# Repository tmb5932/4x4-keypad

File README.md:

# My 4x4 Keypad
This Repo contains the KiCad files of a 4 by 4 Keypad that I personally designed and created (with some help from various KiCad tutorials).

The purpose of this keypad was to bring my Chip8 Emulator to life without taking the easy way out and buying a premade one.

## Author
Travis Brown (tmb5932)

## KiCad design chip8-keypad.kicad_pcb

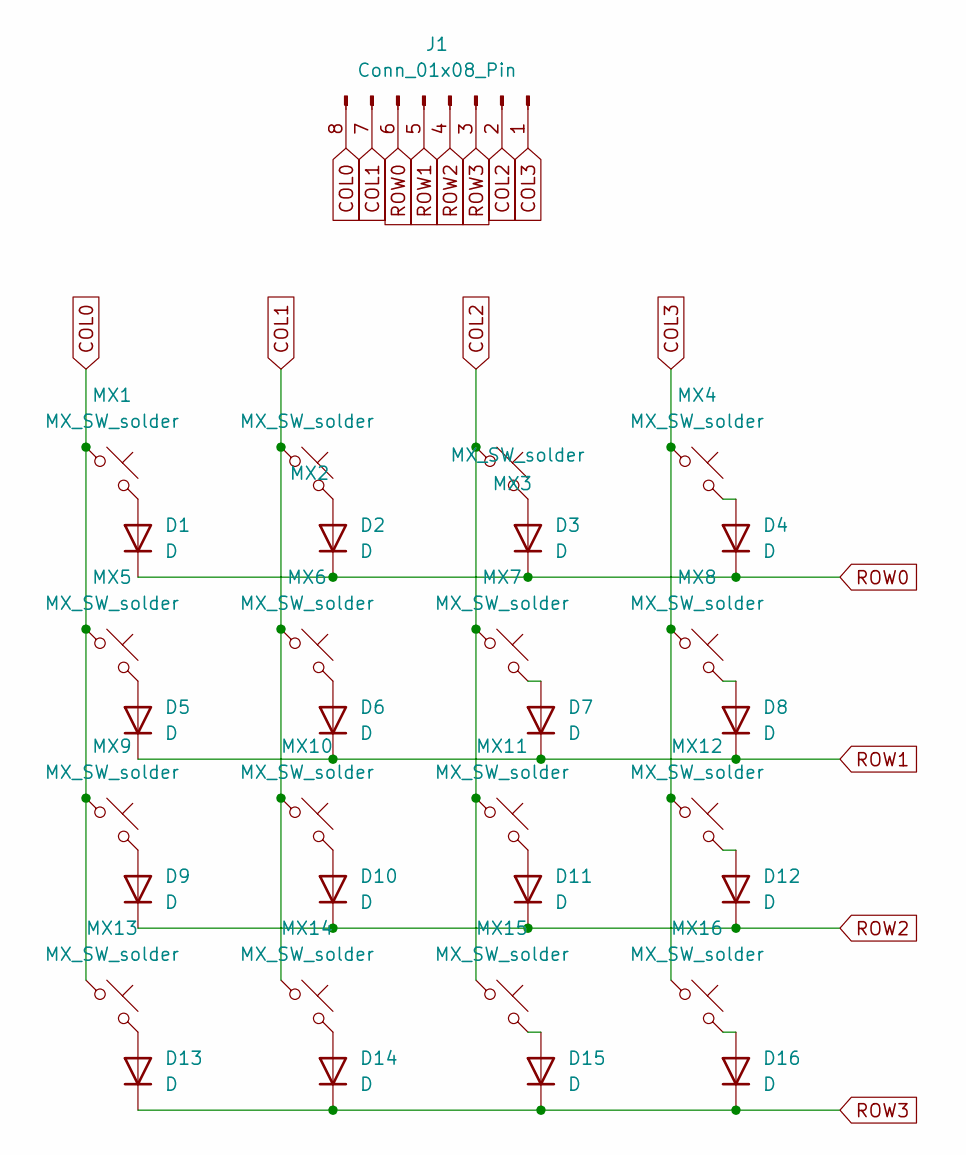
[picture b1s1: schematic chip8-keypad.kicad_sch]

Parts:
D1, D2, D3, D4, D5, D6, D7, D8, D9, D10, D11, D12, D13, D14, D15, D16: D; D_SOD-123
J1: Conn_01x08_Pin; PinHeader_1x08_P2.54mm_Vertical
MX1, MX2, MX3, MX4, MX5, MX6, MX7, MX8, MX9, MX10, MX11, MX12, MX13, MX14, MX15, MX16: MX_SW_solder; SW_MX_1u

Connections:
COL0: J1.8, MX1.1, MX5.1, MX9.1, MX13.1; also elsewhere on the board
COL1: J1.7, MX2.1, MX6.1, MX10.1, MX14.1; also elsewhere on the board
COL2: J1.2, MX3.1, MX7.1, MX11.1, MX15.1; also elsewhere on the board
COL3: J1.1, MX4.1, MX8.1, MX12.1, MX16.1; also elsewhere on the board
unnamed: D1.2 (A), MX1.2
unnamed: D2.2 (A), MX2.2
unnamed: D3.2 (A), MX3.2
unnamed: D4.2 (A), MX4.2
unnamed: D5.2 (A), MX5.2
unnamed: D6.2 (A), MX6.2
unnamed: D7.2 (A), MX7.2
unnamed: D8.2 (A), MX8.2
unnamed: D9.2 (A), MX9.2
unnamed: D10.2 (A), MX10.2
unnamed: D11.2 (A), MX11.2
unnamed: D12.2 (A), MX12.2
unnamed: D13.2 (A), MX13.2
unnamed: D14.2 (A), MX14.2
unnamed: D15.2 (A), MX15.2
unnamed: D16.2 (A), MX16.2
ROW0: D1.1 (K), D2.1 (K), D3.1 (K), D4.1 (K), J1.6; also elsewhere on the board
ROW1: D5.1 (K), D6.1 (K), D7.1 (K), D8.1 (K), J1.5; also elsewhere on the board
ROW2: D9.1 (K), D10.1 (K), D11.1 (K), D12.1 (K), J1.4; also elsewhere on the board
ROW3: D13.1 (K), D14.1 (K), D15.1 (K), D16.1 (K), J1.3; also elsewhere on the board

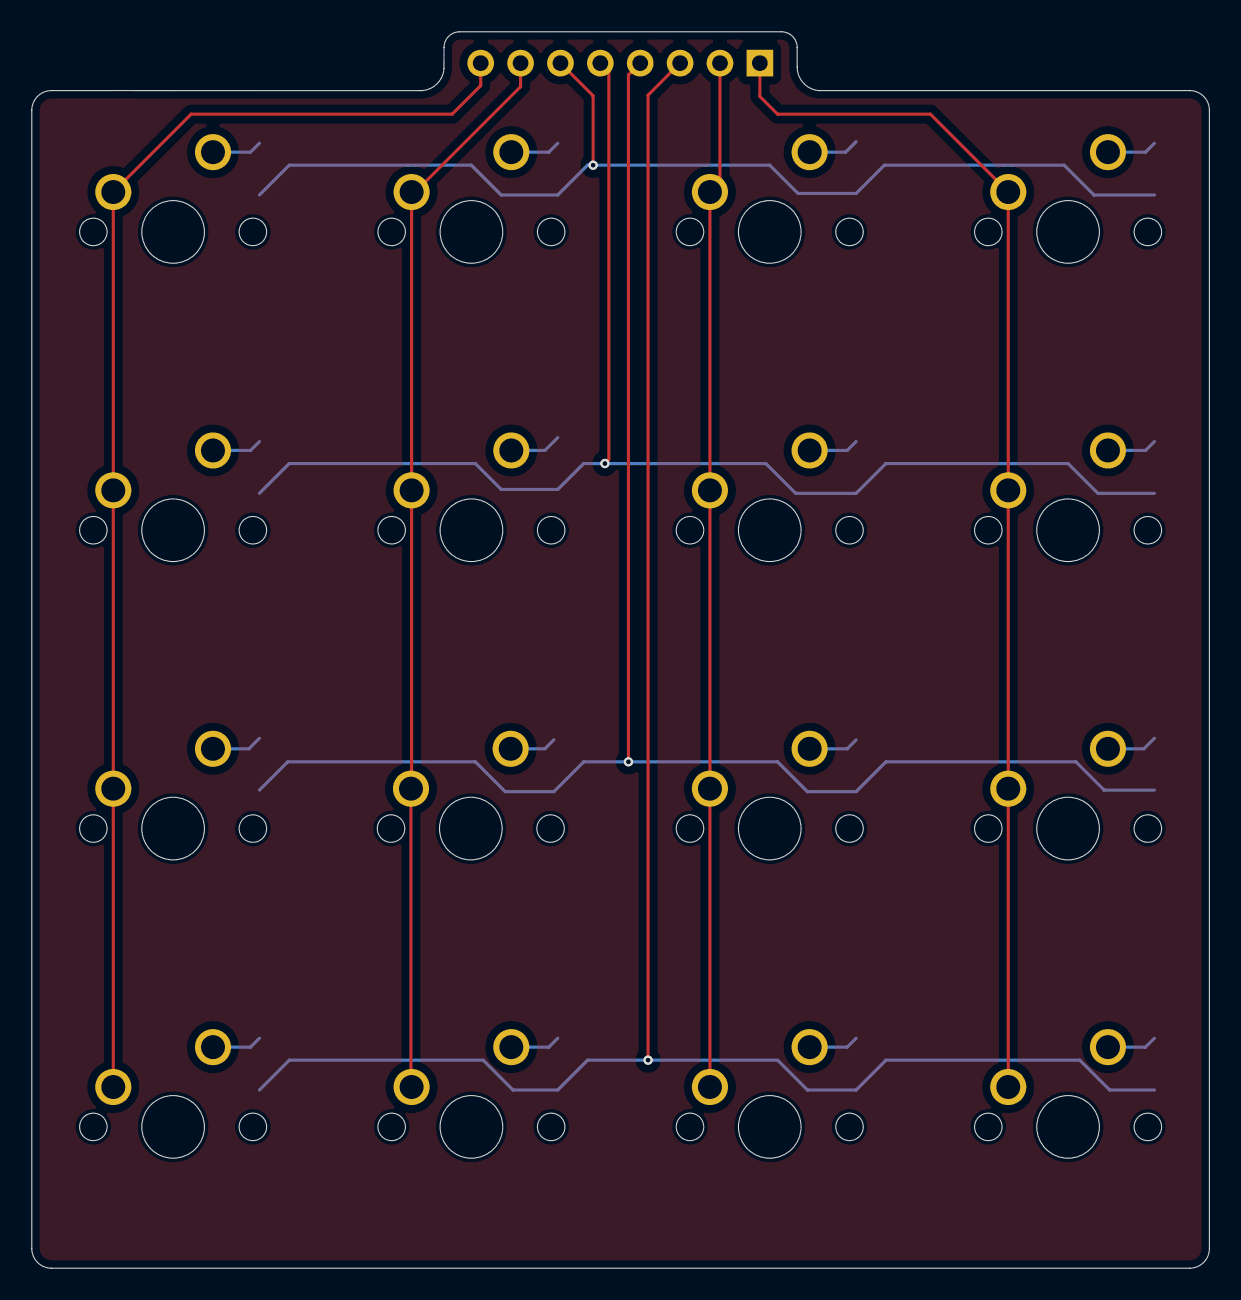
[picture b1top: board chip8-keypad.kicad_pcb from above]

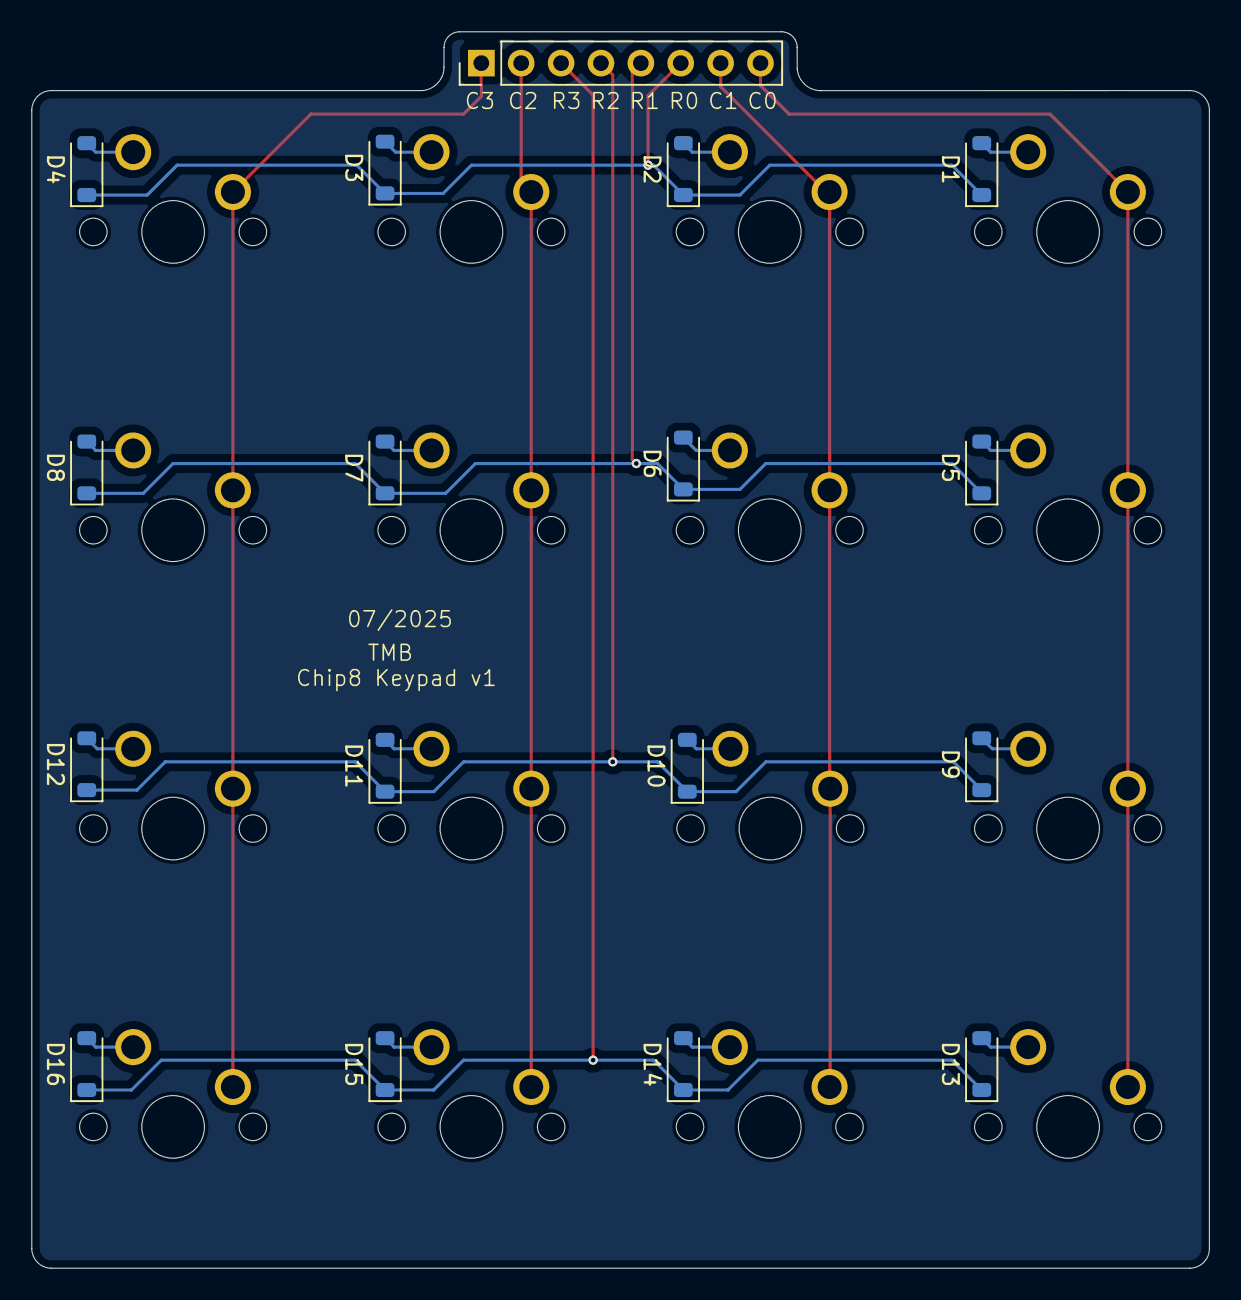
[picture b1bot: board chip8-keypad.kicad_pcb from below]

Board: 2 copper layers, 75.0 x 78.7 mm, 33 parts (17 on the bottom side), 24 nets.

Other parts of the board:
1: Conn_01x08_Pin; PinHeader_1x08_P2.54mm_Vertical

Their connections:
COL0: 1.8; also elsewhere on the board
COL1: 1.7; also elsewhere on the board
COL2: 1.2; also elsewhere on the board
COL3: 1.1; also elsewhere on the board
ROW0: 1.6; also elsewhere on the board
ROW1: 1.5; also elsewhere on the board
ROW2: 1.4; also elsewhere on the board
ROW3: 1.3; also elsewhere on the board

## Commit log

2025-08-28 adding kicad files
